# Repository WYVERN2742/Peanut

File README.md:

# Peanut - Pinenut-01S BL602 MotherBoard

The Peanut is a motherboard for the [PINE64 Pinenut Model-01S](https://pine64.com/product/pinenut-model01s-wifi-ble5-module/) BL602 Wifi/BLE5 Module.

It aims to offer a very large suite of sensors, including Motion, Humidity, Temperature, Ambient Light, and Pressure. While also providing some LEDs and buttons for interaction, with audio output and buzzers for the classic electronic bleeps. It's entirely powered by a single LiFePO4 battery, allowing for easy charging and a compact size.

A prime design point is to also provide capability for extensions; such as solar charging, motor powering, or literally anything else you can imagine.

> [!WARNING]
> This is a hobby project and our first exploration into creating a custom PCB from scratch. Mistakes are Guarenteed!

## Roadmap

- [x] Board Design & Specs
- [x] Component sourcing
- [x] Electronic Schematics
- [x] Breadboard + Devkit prototyping
- [ ] Prototype PCB with contact pads
- [ ] Refinements and Debugging
	- Continual Refinements until design works!
- [ ] Rev 1.0 board
- [ ] Case and Extensions

## Components

> [!NOTE]
> Component list is subject to change; especially before Rev 1.0

[Take a look at the up-to-date table](https://github.com/WYVERN2742/Peanut/issues/3)

## Electronic Schematics:

- [x] Motion Sensor
- [x] Humidity Sensor
- [x] Temperature Sensor
- [x] Ambient Light Sensor
- [x] Digital Muxer
	- [x] Push Buttons
	- [x] Switch
	- [x] LEDs
- [x] DAC
	- [x] Audio Jack
	- [x] Piezo
- [x] ADC
	- [x] Pressure Sensor
	- [x] Battery Monitor

## Design Goals

*User goals and considerations; along with some misc ideas/wants*
- Include Battery + Interfaces for Extension (data & power)
- Small in size;- strap to wrist.
- As many general sensors as possible
- Buttons on battery-side of board if space is constrained
- Buttons should be ergonomic (if mounted length-ways, buttons facing away)

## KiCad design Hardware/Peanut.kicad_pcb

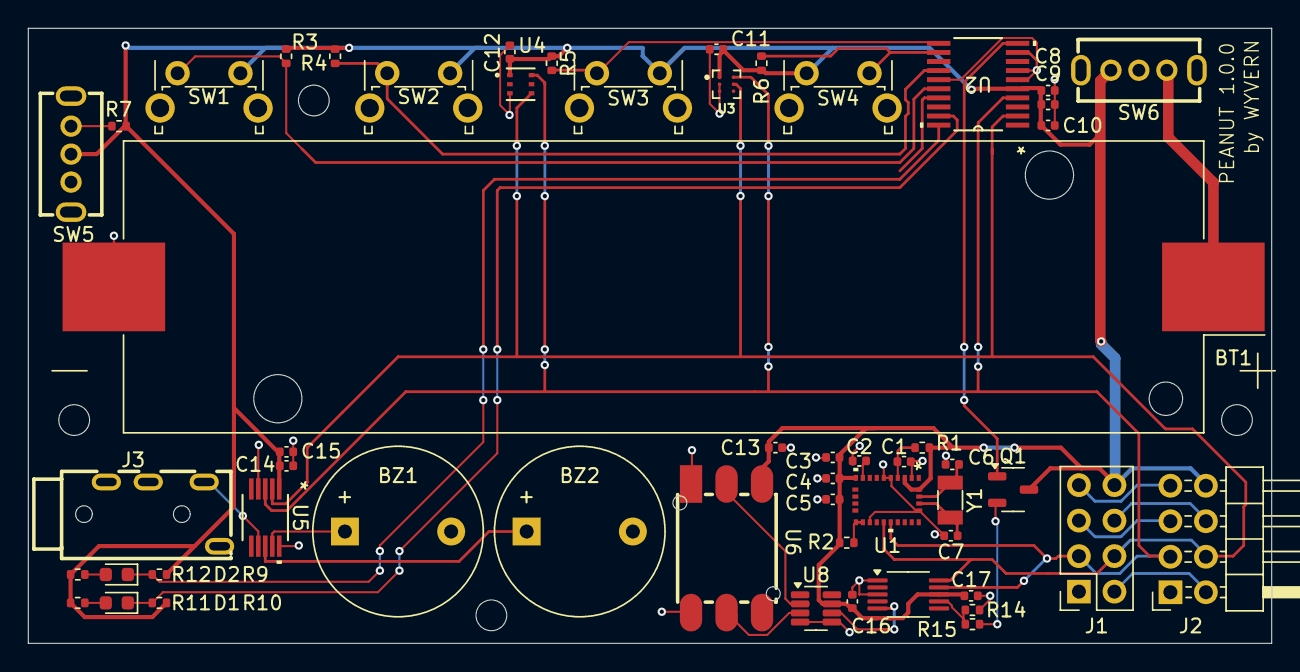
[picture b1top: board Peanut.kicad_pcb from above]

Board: 2 copper layers, 89.0 x 44.0 mm, 54 parts (0 on the bottom side), 32 nets.

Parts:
BT1: 3.3V; BatteryHolder_Keystone_1042_1x18650
BZ1, BZ2: Buzzer; Buzzer_12x9.5RM7.6
C1, C3, C4, C5, C8, C9, C10, C11, C13: 1uF; C_0402_1005Metric
C2, C14, C15: 100nF; C_0402_1005Metric
C6, C7: 22pF; C_0402_1005Metric
C12: 1uf; C_0402_1005Metric
C16, C17: 0.1uF; C_0402_1005Metric
D1: RED; LED_0603_1608Metric
D2: YELLOW; LED_0603_1608Metric
J1: BL602 Female JST Connector; PinSocket_2x04_P2.54mm_Vertical
J2: Extension Male JST Connector; PinHeader_2x04_P2.54mm_Horizontal_Flipped
J3: AudioPlug3; AUDIO-TH_PJ-320A-4P-DIP
Q1: Q_NPN_BEC; SOT-23-3
R1: 10k; R_0402_1005Metric
R2, R11, R12: 2.2k; R_0402_1005Metric
R3, R4, R5, R6, R7, R9, R10: 100k; R_0402_1005Metric
R14, R15: R; R_0402_1005Metric
SW1, SW2, SW3, SW4: Push_Button; SW_Tactile_SPST_Angled_PTS645Vx58-2LFS
SW5, SW6: Slide Switch; SW-TH_SK12D07VG4
U1: BNO085; LGA28_5.2X3.8_CEV
U2: PCF8574APWR; PW20
U3: HDC2010YPAR
U4: LTR-303ALS-01; LTR-308ALS-01_LTO
U5: MCP4728T-E/UN; MSOP10_MC_MCH
U6: LWP040-PSGLC-S; SOP-4_L7.0-W7.0-P2.54-LS10.3-TL-CW_LWP040-PSGLC-S
U7: ADS1015IDGSR; VSSOP-10_3x3mm_P0.5mm
U8: INA350ABSIDDFR; TSOT-23-8
Y1: Crystal_32.768kHz; Crystal_SMD_3215-2Pin_3.2x1.5mm

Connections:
+3V3: C3.1, C4.1, C5.1, C8.1, C9.1, C10.1, C11.1, C12.1, C13.1, C14.2, C15.2, C16.1, C17.1, J1.8, J2.8, Q1.3 (C), R1.2, R2.1, R3.1, R4.1, R5.1, R6.1, R7.1, R9.1, R10.1, R11.1, R12.1, SW1.2, SW2.2, SW3.2, SW4.1, SW5.2, SW6.3, U1.3 (VDD), U1.10 (CLKSEL0), U1.28 (VDDIO), U2.5 (VCC), U3.A1 (VDD), U4.1 (VDD), U5.1 (VDD), U6.3 (VIN+), U7.8 (VDD), U8.7 (V+)
/DigitalMuxer/P2: Q1.1 (B), U2.10 (P0)
GND: BT1.2 (-), BZ1.2 (-), BZ2.2 (-), C1.2, C2.1, C3.2, C4.2, C5.2, C6.2, C7.2, C8.2, C9.2, C10.2, C11.2, C12.2, C13.2, C14.1, C15.1, C16.2, C17.2, J1.1, J2.1, J3.S, R15.2, SW5.3, U1.2 (GND), U1.5 (PS1), U1.6 (PS0/WAKE), U1.17 (SA0/H_MOSI), U1.25 (GNDIO), U2.6 (A0), U2.7 (A1), U2.9 (A2), U2.15 (GND), U3.B1 (ADDR), U3.C1 (GND), U4.3 (GND), U5.4 (~LDAC), U5.10 (VSS), U6.1 (GND), U6.6 (GND), U7.1 (ADDR), U7.3 (GND), U8.4 (V-), U8.5 (REF)
unnamed: BT1.1 (+), SW6.1
unnamed: BZ1.1 (+), U5.9 (VOUTD)
unnamed: BZ2.1 (+), U5.8 (VOUTC)
unnamed: D1.2 (A), R11.2
unnamed: D1.1 (K), R10.2, U2.19 (P6)
unnamed: D2.2 (A), R12.2
unnamed: D2.1 (K), R9.2, U2.20 (P7)
unnamed: J1.5, J2.5
unnamed: J1.6, J2.6
unnamed: Q1.2 (E), R14.1
unnamed: C1.1, R1.1, U1.4 (BOOTN)
unnamed: C2.2, U1.9 (CAP)
unnamed: R2.2, U1.15 (S_SCL), U1.16 (S_SDA)
unnamed: C6.1, U1.27 (XIN32), Y1.1
unnamed: C7.1, U1.26 (XOUT32/CLKSEL1), Y1.2
unnamed: R5.2, SW3.1, U2.11 (P1)
unnamed: R6.2, SW4.2, U2.12 (P2)
unnamed: R4.2, SW2.1, U2.14 (P3)
unnamed: R3.2, SW1.1, U2.16 (P4)
unnamed: R7.2, SW5.1, U2.17 (P5)
unnamed: J3.T, U5.7 (VOUTB)
unnamed: U6.2 (VOUT+), U8.2 (-)
unnamed: U6.5 (VOUT-), U8.3 (+)
unnamed: U7.5 (AIN1), U8.6
unnamed: R14.2, R15.1, U7.7 (AIN3)
SCL: J1.4, J2.4, U1.19 (H_SCL/SCK/RX), U2.2 (SCL), U3.B2 (SCL), U4.4 (SCL), U5.2 (SCL), U7.10 (SCL)
SDA: J1.3, J2.3, U1.20 (H_SDA/H_MISO/TX), U2.4 (SDA), U3.A2 (SDA), U4.6 (SDA), U5.3 (SDA), U7.9 (SDA)
UART_RX: J1.7, J2.7
UART_TX: J1.2, J2.2

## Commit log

2024-04-07 Quick user design goals
2024-04-07 Convert readme to GithubMD
2024-04-10 Add Temperature and Humidity Sensor
2024-04-10 Add bypass cap to humid, and fix add grounding
2024-04-11 Ambient Light Sensor
2024-05-05 Use tags for nets, apply netgroups, mess around in pcb view
2024-05-06 Update board layout
2024-05-06 Remove kicad backup directory
2024-05-06 Add Component diagram
    closes #4
2024-05-06 Add component diagram to readme
2024-05-07 Datasheets and footprints for some components
2024-05-07 Import 3D and Footprints for most components
2024-05-07 Use Peanut symbols, fix ERC errors, progress on DAC & Pressure
2024-05-07 Move Render to top of README
2024-05-12 Update roadmap - Added board design & specs - Explicit mention of prototype PCB
2024-06-09 Replace 1 LED with battery measurement toggle - We require an additional IO to toggle battery draining for % measurement, however we had no more ports. After a group discussion, one LED was dropped.
2024-06-09 Add Battery Monitoring & Use Project Parts Library
2024-06-09 Update DAC and ADC on roadmap
2024-06-09 Update README.md
    Ticked off component sourcing on the roadmap.
2024-07-03 Fully wired board!
2024-11-09 wip: i2c debugging
2024-11-24 Initial OS architecture, and updated PCB work After a joint planning session, designed and architected OS structure: ``` src/ |- os: Audio, Accelerometer, Humidity, etc |- drivers: I2C interfaces, pe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
2024-12-01 Library structure, PCF impl
2024-12-01 Outline finished for the BNO085 and sh2 modules. Created following Adafruit's implementation.
2024-12-01 PCF8574 Drivers and example now working on the devkit!
2024-12-01 - Peanut lib description - format with tabs
2024-12-02 ADS and INA datasheets
2024-12-02 Updates to PCB and ADC Schematics
    - Swapped audio jack to correct pin (4P-DIP)
    - Add LCSC numbers for all components
    - Reroute some sensitive signal traces
    - Add Board rev and author
    - add 4x M2 mounting holes
    - fixup some misc silkscreen, footprints, and component 3d models
2024-12-08 VScode rust-analyzer support
    - Add in `-Z unstable-options` to fix issue with `--keep-going`
    - Don't build all targets (including the unimplemented `test` target) by default
2024-12-08 Use atomic whitespace for indentation
2024-12-08 Update sh2.rs
    Reworked the SH-2 module to exclude items relating directly to the BNO.
    Added structs for data passed/received through SH-2, and a little bit of impl. Still a work in progress.
2024-12-08 Implement Peanut object Implement LED OS drivers No longer pass i2c on construction
